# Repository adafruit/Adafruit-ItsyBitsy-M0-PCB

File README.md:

## Adafruit ItsyBitsy M0 microcontroller breakout PCB

<a href="http://www.adafruit.com/products/3727"><br/>
Click here to purchase one from the Adafruit shop</a>

PCB files for the Adafruit ItsyBitsy M0. PCB format is EagleCAD schematic and board layout

For more details, check out the product pages at
* https://www.adafruit.com/products/3727

### Description

What's smaller than a Feather but larger than a Trinket? It's an Adafruit ItsyBitsy M0 Express! Small, powerful, with a rockin' ATSAMD21 Cortex M0 processor running at 48 MHz - this microcontroller board is perfect when you want something very compact, but still with a bunch of pins.

ItsyBitsy M0 Express is only 1.4" long by 0.7" wide, but has 6 power pins, 23 digital GPIO pins (12 of which can be analog in, 1x analog out, and 13x PWM out). It's the same chip as the Arduino Zero and packs much of the same capability as an Adafruit Metro M0 Express or Feather M0 Express but really really small. So it's great once you've finished up a prototype on a Metro M0 or Feather M0, and want to make the project much smaller. It even comes with 2MB of SPI Flash built in, for data logging, file storage, or CircuitPython code.

The most exciting part of the ItsyBitsy M0 is that while you can use it with the Arduino IDE, we are shipping it with CircuitPython on board. When you plug it in, it will show up as a very small disk drive with main.py on it. Edit main.py with your favorite text editor to build your project using Python, the most popular programming language. No installs, IDE or compiler needed, so you can use it on any computer, even ChromeBooks or computers you can't install software on. When you're done, unplug the Itsy' and your code will go with you.

### License

Adafruit invests time and resources providing this open source design, please support Adafruit and open-source hardware by purchasing products from [Adafruit](https://www.adafruit.com)!

Designed by Limor Fried/Ladyada for Adafruit Industries.

Creative Commons Attribution/Share-Alike, all text above must be included in any redistribution. See license.txt for additional details.

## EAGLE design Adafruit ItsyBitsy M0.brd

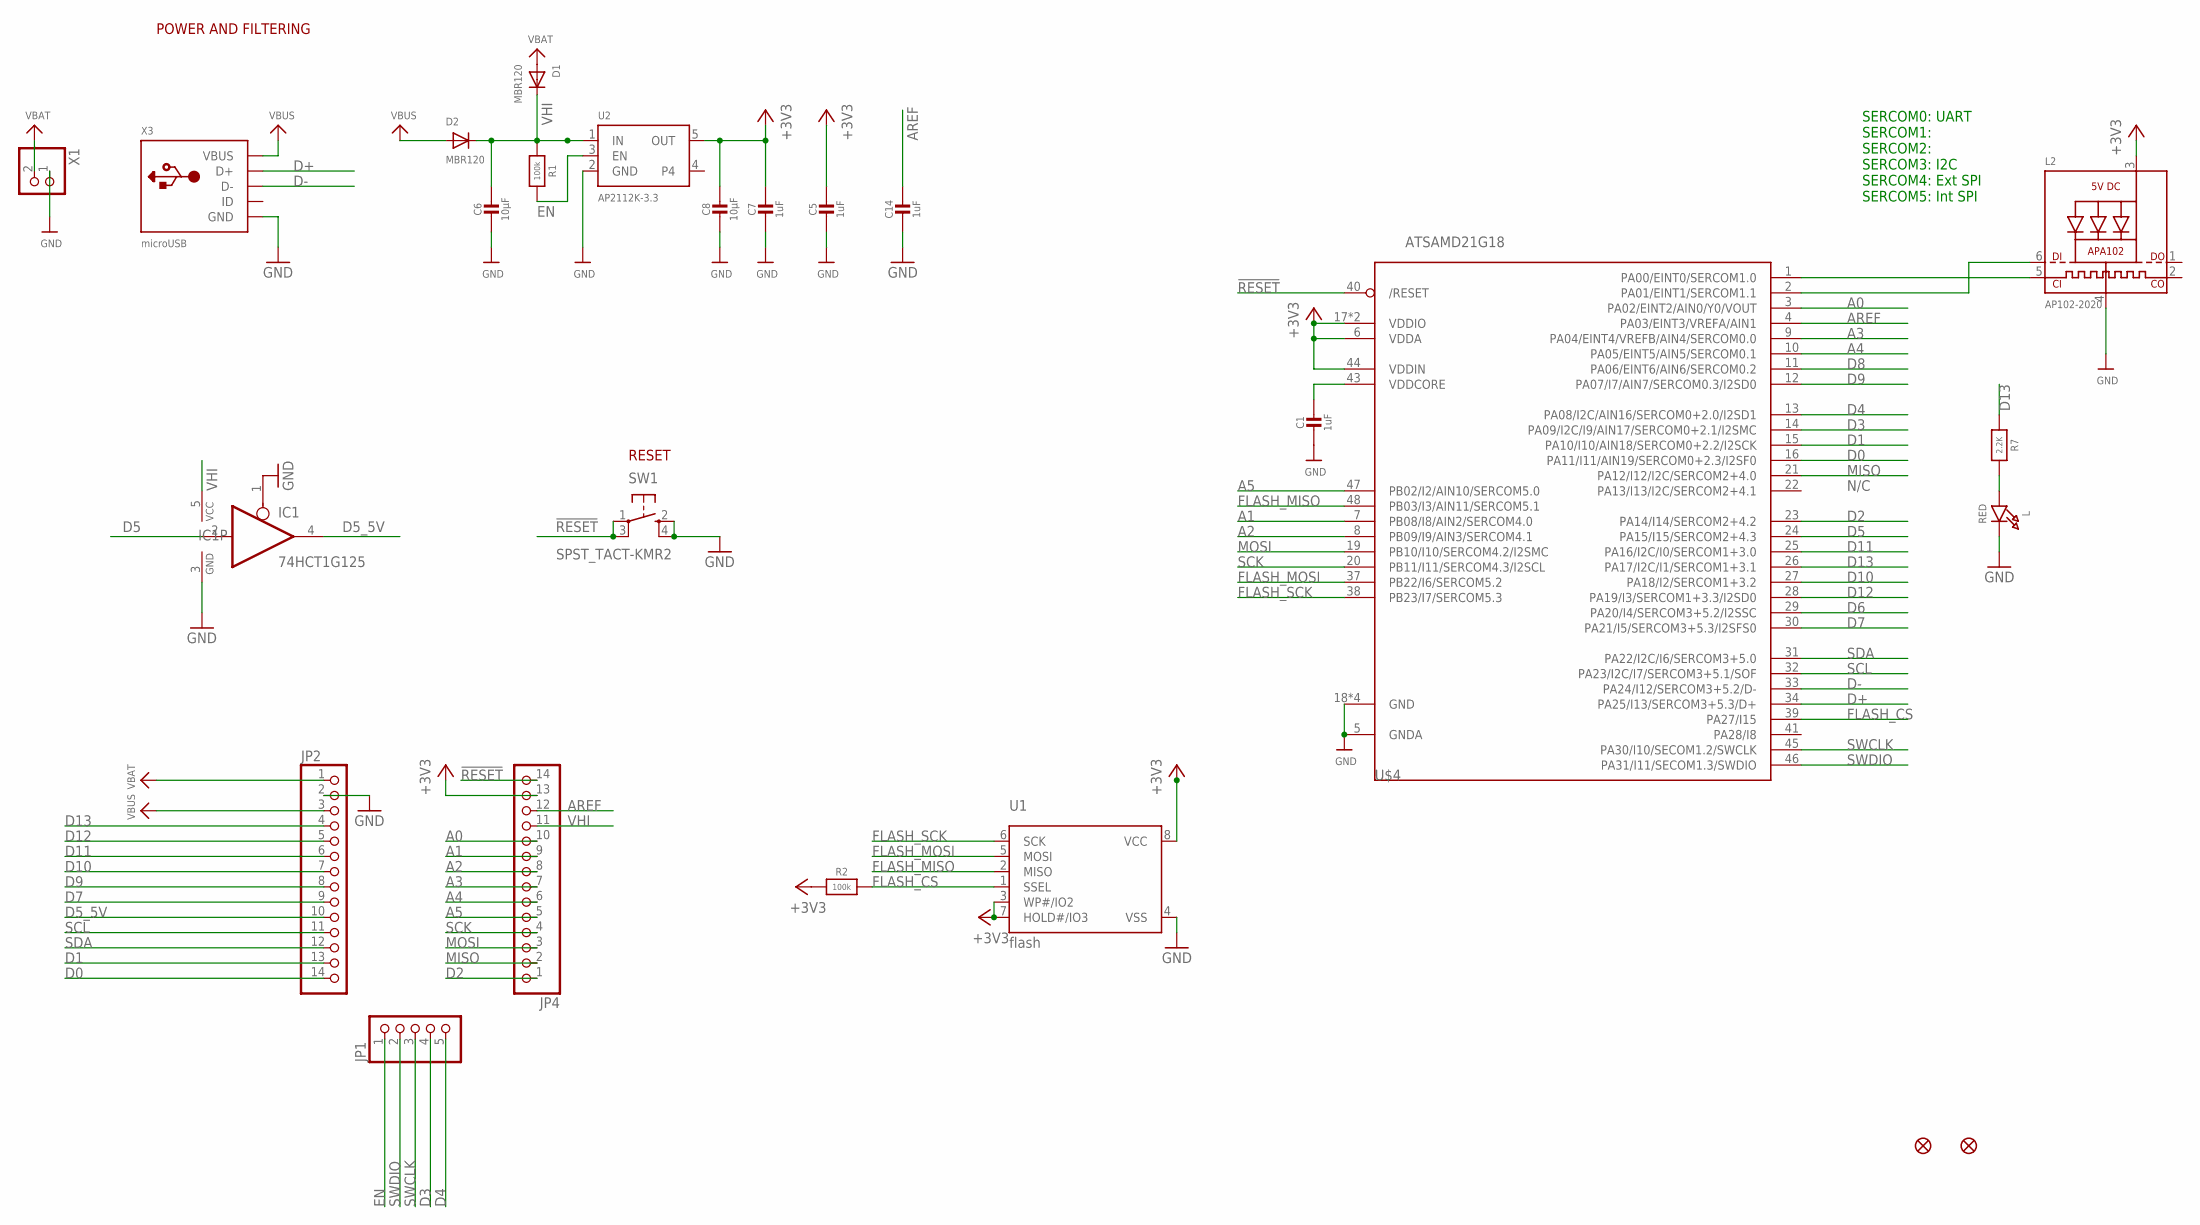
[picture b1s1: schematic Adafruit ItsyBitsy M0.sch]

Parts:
C1, C5, C7, C14: 1uF; 0603-NO
C6, C8: 10µF; 0805-NO
D1, D2: MBR120; SOD-123FL
IC1: 74HCT1G125; SOT23-5
JP1: HEADER-1X570MIL; 1X05_ROUND_70
JP2, JP4: HEADER-1X14; 1X14_ROUND70
L: RED; CHIPLED_0805_NOOUTLINE
L2: AP102-2020; APA102_2020
R1, R2: 100k; 0603-NO
R7: 2.2K; 0603-NO
SW1: SPST_TACT-KMR2; KMR2
U1: flash; USON8
U2: AP2112K-3.3; SOT23-5
U$4: ATSAMD21G18; TQFN48_7MM
U$34, U$35: FIDUCIAL_1MM
X1: CON_JST_PH_2PIN; JSTPH2
X3: microUSB; 4UCONN_20329_V2

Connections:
!RESET: JP4.14, SW1.1, SW1.3 (P1), U$4.40 (/RESET)
+3V3: C5.1, C7.1, C8.1, JP4.13, L2.3 (VDD), R2.1, U1.3 (WP#/IO2), U1.7 (HOLD#/IO3), U1.8 (VCC), U2.5 (OUT), U$4.6 (VDDA), U$4.17 (VDDIO), U$4.36 (VDDIO), U$4.44 (VDDIN)
A0: JP4.10, U$4.3 (PA02/EINT2/AIN0/Y0/VOUT)
A1: JP4.9, U$4.7 (PB08/I8/AIN2/SERCOM4.0)
A2: JP4.8, U$4.8 (PB09/I9/AIN3/SERCOM4.1)
A3: JP4.7, U$4.9 (PA04/EINT4/VREFB/AIN4/SERCOM0.0)
A4: JP4.6, U$4.10 (PA05/EINT5/AIN5/SERCOM0.1)
A5: JP4.5, U$4.47 (PB02/I2/AIN10/SERCOM5.0)
AREF: C14.1, JP4.12, U$4.4 (PA03/EINT3/VREFA/AIN1)
D0: JP2.14, U$4.16 (PA11/I11/AIN19/SERCOM0+2.3/I2SF0)
D1: JP2.13, U$4.15 (PA10/I10/AIN18/SERCOM0+2.2/I2SCK)
D2: JP4.1, U$4.23 (PA14/I14/SERCOM2+4.2)
D3: JP1.4, U$4.14 (PA09/I2C/I9/AIN17/SERCOM0+2.1/I2SMC)
D4: JP1.5, U$4.13 (PA08/I2C/AIN16/SERCOM0+2.0/I2SD1)
D5: IC1.2 (I), U$4.24 (PA15/I15/SERCOM2+4.3)
D5_5V: IC1.4 (O), JP2.10
D6: U$4.29 (PA20/I4/SERCOM3+5.2/I2SSC)
D7: JP2.9, U$4.30 (PA21/I5/SERCOM3+5.3/I2SFS0)
D8: U$4.11 (PA06/EINT6/AIN6/SERCOM0.2)
D9: JP2.8, U$4.12 (PA07/I7/AIN7/SERCOM0.3/I2SD0)
D10: JP2.7, U$4.27 (PA18/I2/SERCOM1+3.2)
D11: JP2.6, U$4.25 (PA16/I2C/I0/SERCOM1+3.0)
D12: JP2.5, U$4.28 (PA19/I3/SERCOM1+3.3/I2SD0)
D13: JP2.4, R7.1, U$4.26 (PA17/I2C/I1/SERCOM1+3.1)
D+: U$4.34 (PA25/I13/SERCOM3+5.3/D+), X3.D+
D-: U$4.33 (PA24/I12/SERCOM3+5.2/D-), X3.D-
EN: JP1.1, R1.2, U2.3 (EN)
FLASH_CS: R2.2, U1.1 (SSEL), U$4.39 (PA27/I15)
FLASH_MISO: U1.2 (MISO), U$4.48 (PB03/I3/AIN11/SERCOM5.1)
FLASH_MOSI: U1.5 (MOSI), U$4.37 (PB22/I6/SERCOM5.2)
FLASH_SCK: U1.6 (SCK), U$4.38 (PB23/I7/SERCOM5.3)
GND: C1.2, C5.2, C6.2, C7.2, C8.2, C14.2, IC1.1 (OE), IC1.3 (GND), JP2.2, L.C, L2.4 (GND), SW1.2 (S), SW1.4 (S1), U1.4 (VSS), U2.2 (GND), U$4.5 (GNDA), U$4.18 (GND), U$4.35 (GND), U$4.42 (GND), U$4.THERMAL (GND), X1.1, X3.BASE@1 (GND), X3.BASE@2 (GND), X3.GND, X3.SPRT@1 (GND), X3.SPRT@2 (GND), X3.SPRT@3 (GND), X3.SPRT@4 (GND)
MISO: JP4.2, U$4.21 (PA12/I12/I2C/SERCOM2+4.0)
MOSI: JP4.3, U$4.19 (PB10/I10/SERCOM4.2/I2SMC)
unnamed: L2.5 (CKI), U$4.1 (PA00/EINT0/SERCOM1.0)
unnamed: L.A, R7.2
unnamed: L2.6 (DI), U$4.2 (PA01/EINT1/SERCOM1.1)
SCK: JP4.4, U$4.20 (PB11/I11/SERCOM4.3/I2SCL)
SCL: JP2.11, U$4.32 (PA23/I2C/I7/SERCOM3+5.1/SOF)
SDA: JP2.12, U$4.31 (PA22/I2C/I6/SERCOM3+5.0)
SWCLK: JP1.3, U$4.45 (PA30/I10/SECOM1.2/SWCLK)
SWDIO: JP1.2, U$4.46 (PA31/I11/SECOM1.3/SWDIO)
VBAT: D1.A, JP2.1, X1.2
VBUS: D2.A, JP2.3, X3.VBUS
VDDCORE: C1.1, U$4.43 (VDDCORE)
VHI: C6.1, D1.C, D2.C, IC1.5 (VCC), JP4.11, R1.1, U2.1 (IN)

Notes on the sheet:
POWER AND FILTERING
RESET
N/C
SERCOM0: UART SERCOM1: SERCOM2: SERCOM3: I2C SERCOM4: Ext SPI SERCOM5: Int SPI

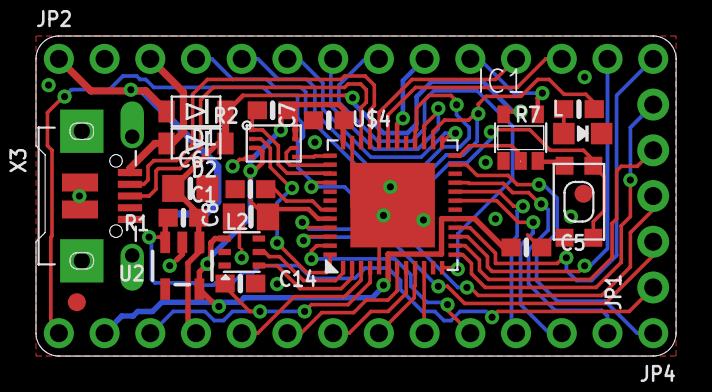
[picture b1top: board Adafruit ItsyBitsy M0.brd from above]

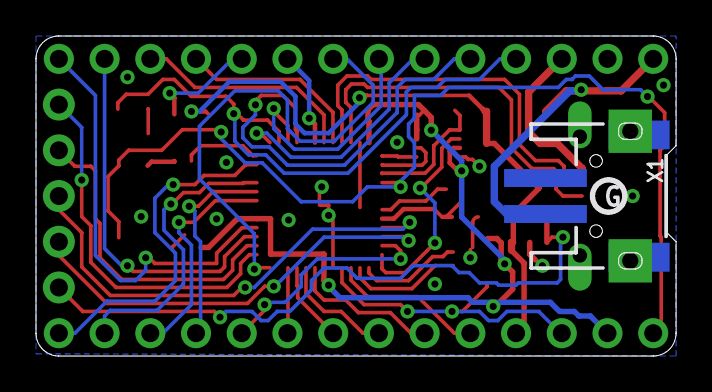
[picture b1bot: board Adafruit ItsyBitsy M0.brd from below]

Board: 2 copper layers, 35.6 x 17.8 mm, 28 parts (3 on the bottom side), 44 nets.

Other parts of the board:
U$13: PCBFEAT-REV-040
U$14: ITSYM0_TOP
U$15: ITSYM0_BOT

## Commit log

2018-03-14 init
2021-05-18 Add pinout PDF

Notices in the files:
parts and their libraries:
microbuilder: This work is placed in the public domain, and may be freely used for commercial and non-commercial work with the following conditions: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
